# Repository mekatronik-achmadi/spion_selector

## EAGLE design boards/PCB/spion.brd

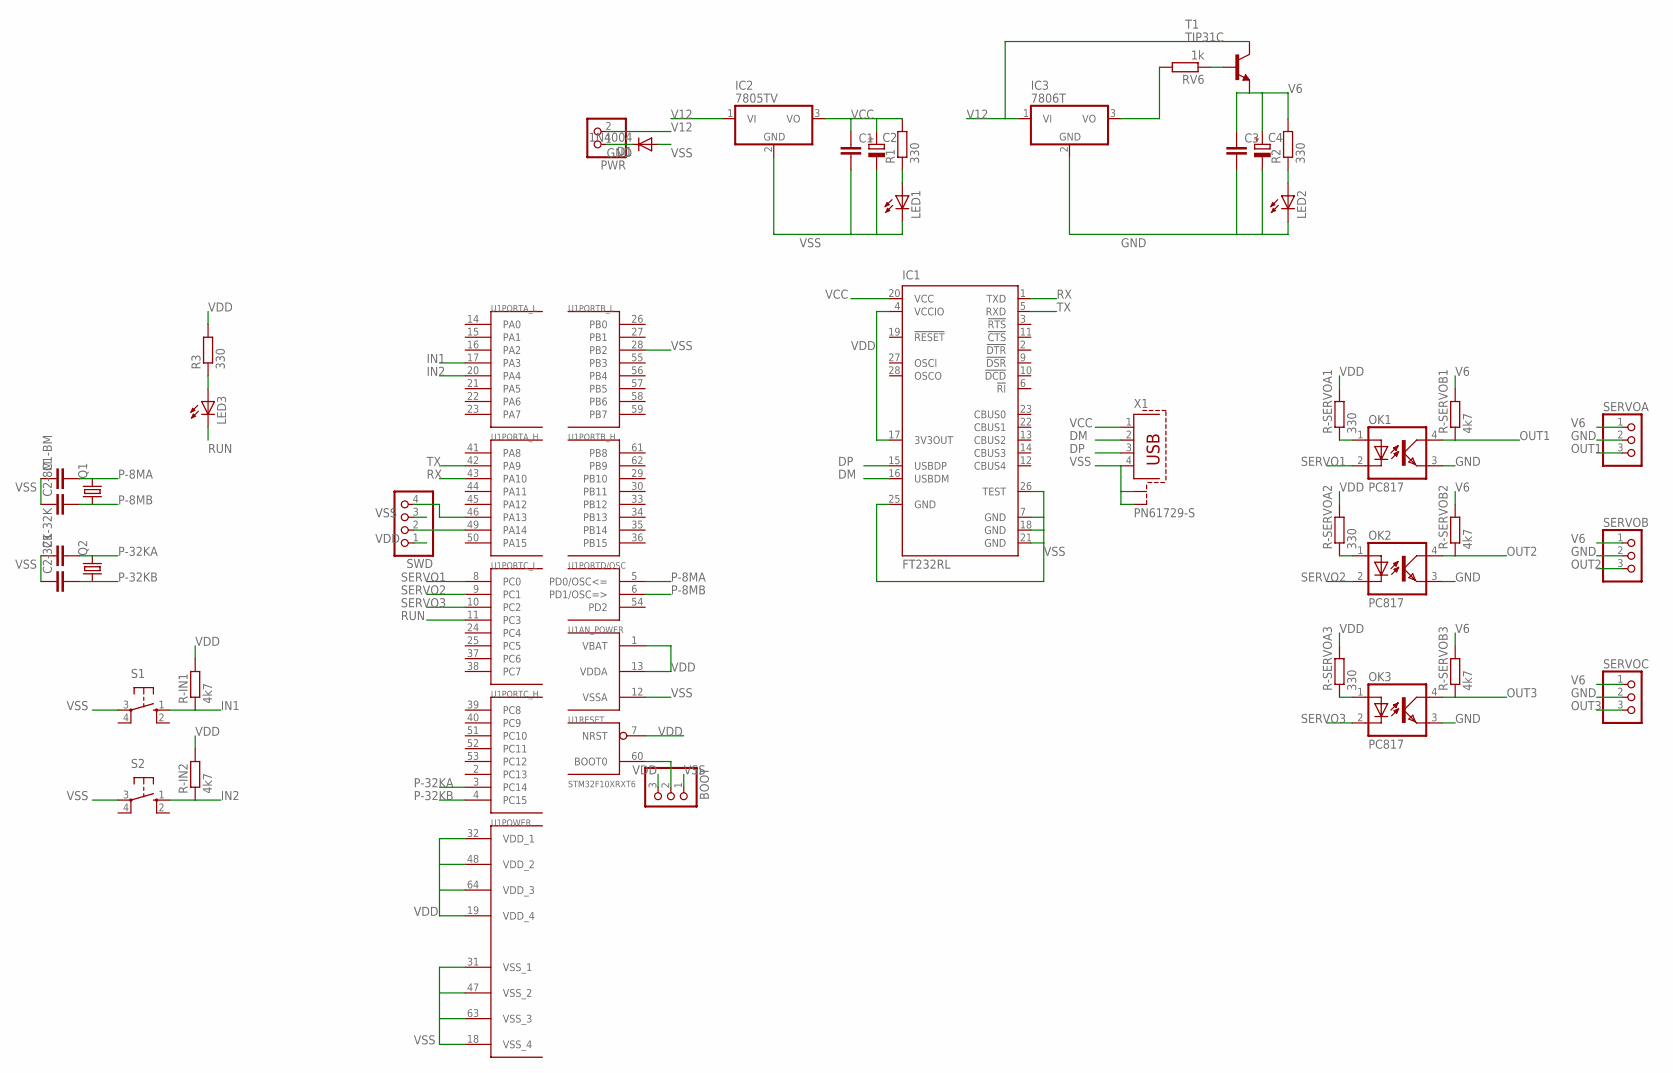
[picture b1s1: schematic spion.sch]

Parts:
BOOT: PINHD-1X3; 1X03
C1, C1-32K, C1-BM, C2-8M, C2-32K, C3: C-EU025-024X044; C025-024X044
C2, C4: CPOL-EUE2-5; E2-5
D1: 1N4004; DO41-10
IC1: FT232RL; SSOP28
IC2: 7805TV; TO220V
IC3: 7806T; TO220H
LED1, LED2, LED3: LED3MM
OK1, OK2, OK3: PC817; DIL04
PWR: PINHD-1X2; 1X02
Q1: CRYSTALHC49S; HC49/S
Q2: CRYSTALTC26V; TC26V
R1, R2, R3: 330; 0204/7
R-IN1, R-IN2: 4k7; 0204/7
R-SERVOA1, R-SERVOA2, R-SERVOA3: 330; 0204/7
R-SERVOB1, R-SERVOB2, R-SERVOB3: 4k7; 0204/7
RV6: 1k; 0204/7
S1, S2: 10-XX; B3F-10XX
SERVOA: PINHD-1X3; 1X03
SERVOB: PINHD-1X3; 1X03
SERVOC: PINHD-1X3; 1X03
SWD: PINHD-1X4; 1X04
T1: TIP31C; TO220
U1: STM32F10XRXT6; TQFP64
X1: PN61729-S

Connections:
DM: IC1.16 (USBDM), X1.2
DP: IC1.15 (USBDP), X1.3
GND: C3.2, C4.-, D1.C, IC3.2 (GND), LED2.K (C), OK1.3 (EMIT), OK2.3 (EMIT), OK3.3 (EMIT), PWR.1, SERVOA.2, SERVOB.2, SERVOC.2
IN1: R-IN1.1, S1.1 (S), U1.17 (PA3)
IN2: R-IN2.1, S2.1 (S), U1.20 (PA4)
unnamed: SWD.2, U1.49 (PA14)
unnamed: SWD.4, U1.46 (PA13)
unnamed: BOOT.2, U1.60 (BOOT0)
unnamed: OK1.1 (A), R-SERVOA1.1
unnamed: LED3.A, R3.1
unnamed: IC3.3 (VO), RV6.2
unnamed: OK2.1 (A), R-SERVOA2.1
unnamed: RV6.1, T1.1 (B)
unnamed: OK3.1 (A), R-SERVOA3.1
unnamed: LED1.A, R1.1
unnamed: LED2.A, R2.1
OUT1: OK1.4 (COL), R-SERVOB1.1, SERVOA.3
OUT2: OK2.4 (COL), R-SERVOB2.1, SERVOB.3
OUT3: OK3.4 (COL), R-SERVOB3.1, SERVOC.3
P-8MA: C1-BM.2, Q1.2, U1.5 (PD0/OSC<=)
P-8MB: C2-8M.2, Q1.1, U1.6 (PD1/OSC=>)
P-32KA: C1-32K.2, Q2.2, U1.3 (PC14)
P-32KB: C2-32K.2, Q2.1, U1.4 (PC15)
RUN: LED3.K (C), U1.11 (PC3)
RX: IC1.1 (TXD), U1.43 (PA10)
SERVO1: OK1.2 (C), U1.8 (PC0)
SERVO2: OK2.2 (C), U1.9 (PC1)
SERVO3: OK3.2 (C), U1.10 (PC2)
TX: IC1.5 (RXD), U1.42 (PA9)
V6: C3.1, C4.+, R2.2, R-SERVOB1.2, R-SERVOB2.2, R-SERVOB3.2, SERVOA.1, SERVOB.1, SERVOC.1, T1.3 (E)
V12: IC2.1 (VI), IC3.1 (VI), PWR.2, T1.2 (C)
VCC: C1.1, C2.+, IC1.20 (VCC), IC2.3 (VO), R1.2, X1.1
VDD: BOOT.3, IC1.4 (VCCIO), IC1.17 (3V3OUT), R3.2, R-IN1.2, R-IN2.2, R-SERVOA1.2, R-SERVOA2.2, R-SERVOA3.2, SWD.1, U1.1 (VBAT), U1.7 (NRST), U1.13 (VDDA), U1.19 (VDD_4), U1.32 (VDD_1), U1.48 (VDD_2), U1.64 (VDD_3)
VSS: BOOT.1, C1.2, C1-32K.1, C1-BM.1, C2.-, C2-8M.1, C2-32K.1, D1.A, IC1.7 (GND), IC1.18 (GND), IC1.21 (GND), IC1.25 (GND), IC1.26 (TEST), IC2.2 (GND), LED1.K (C), S1.3, S2.3, SWD.3, U1.12 (VSSA), U1.18 (VSS_4), U1.28 (PB2), U1.31 (VSS_1), U1.47 (VSS_2), U1.63 (VSS_3), X1.4, X1.S1, X1.S2

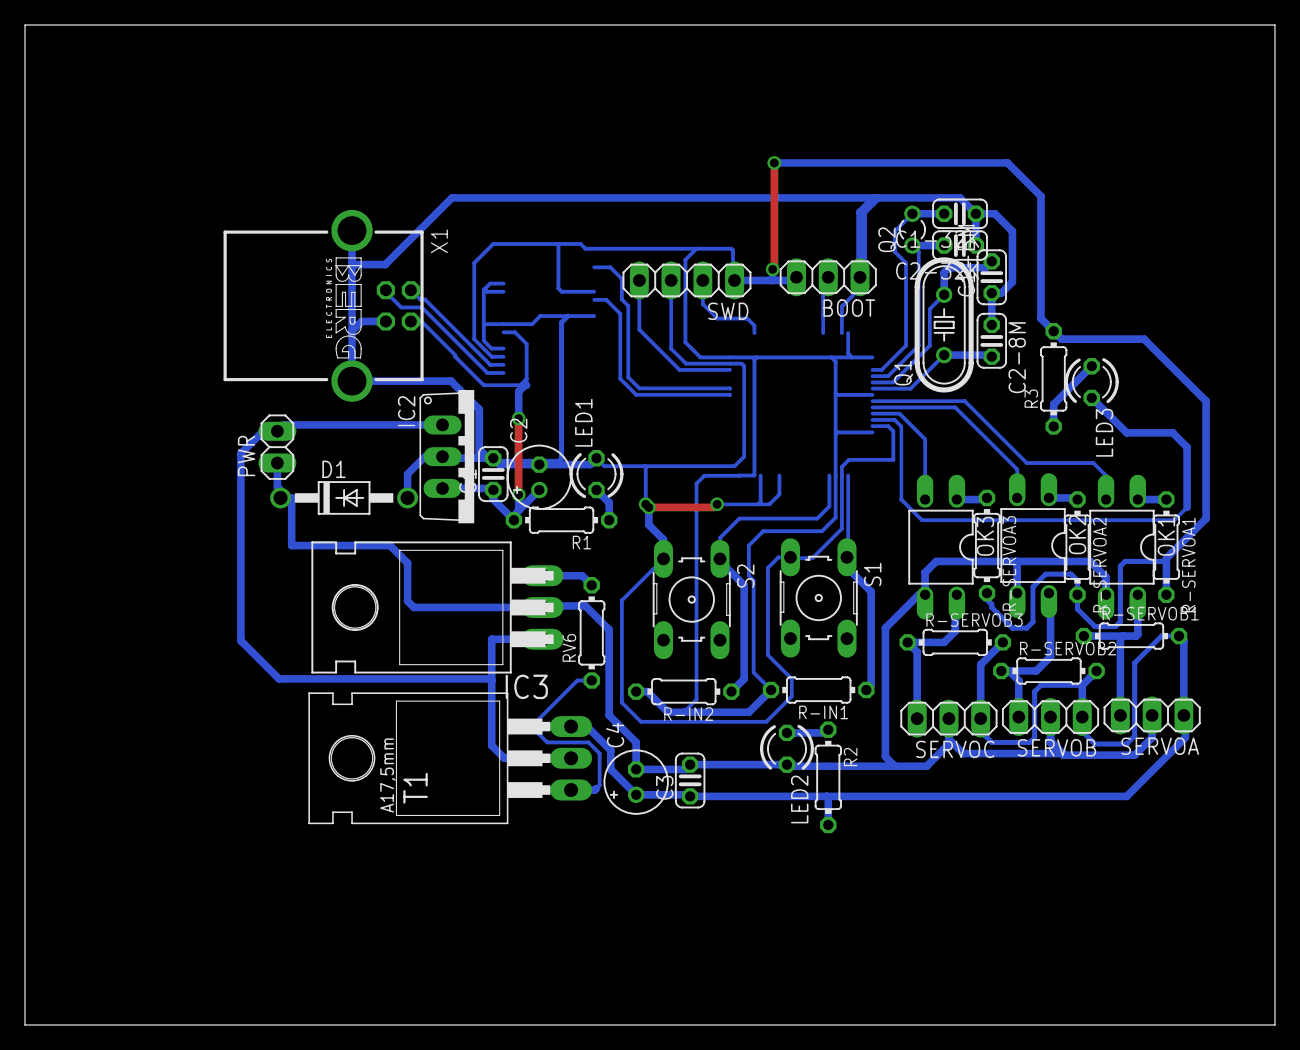
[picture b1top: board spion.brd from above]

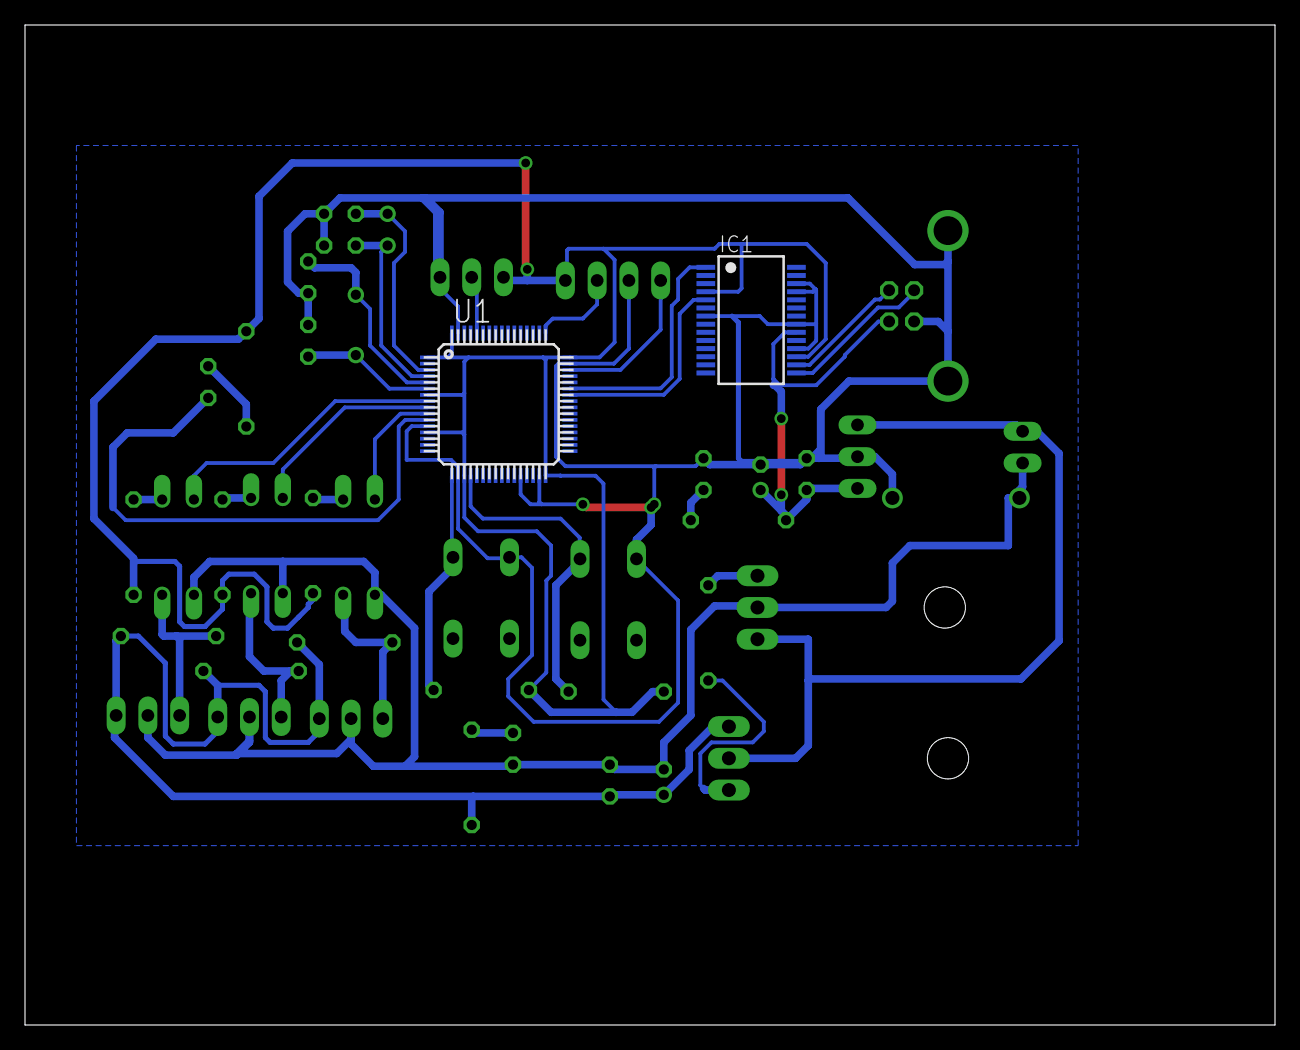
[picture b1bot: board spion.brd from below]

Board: 2 copper layers, 100.0 x 80.0 mm, 43 parts (2 on the bottom side), 34 nets.

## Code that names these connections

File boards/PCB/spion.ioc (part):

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Mcu.Name=STM32F103R(8-B)Tx
Mcu.Package=LQFP64
PA10.Mode=Asynchronous
PA10.Signal=USART1_RX
PA13.Mode=Serial-Wire
PA13.Signal=SYS_JTMS-SWDIO
PA14.Mode=Serial-Wire
PA14.Signal=SYS_JTCK-SWCLK
PA3.Signal=GPIO_Input
PA4.Signal=GPIO_Input
PA9.Mode=Asynchronous
PA9.Signal=USART1_TX
PB2.Signal=GPIO_Input
PC0.Signal=GPIO_Output
PC1.Signal=GPIO_Output
PC14-OSC32_IN.Mode=LSE-External-Oscillator
PC14-OSC32_IN.Signal=SYS_OSC32_IN
PC15-OSC32_OUT.Mode=LSE-External-Oscillator
PC15-OSC32_OUT.Signal=SYS_OSC32_OUT
PC2.Signal=GPIO_Output
PC3.Signal=GPIO_Output
PD0-OSC_IN.Mode=HSE-External-Oscillator
PD0-OSC_IN.Signal=SYS_OSC_IN
PD1-OSC_OUT.Mode=HSE-External-Oscillator
PD1-OSC_OUT.Signal=SYS_OSC_OUT

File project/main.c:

/*
    ChibiOS/RT - Copyright (C) 2006-2013 Giovanni Di Sirio

    Licensed under the Apache License, Version 2.0 (the "License");
    you may not use this file except in compliance with the License.
    You may obtain a copy of the License at

        http://www.apache.org/licenses/LICENSE-2.0

    Unless required by applicable law or agreed to in writing, software
    distributed under the License is distributed on an "AS IS" BASIS,
    WITHOUT WARRANTIES OR CONDITIONS OF ANY KIND, either express or implied.
    See the License for the specific language governing permissions and
    limitations under the License.
*/

#include "srcconf.h"

#define run 3
#define run_on palClearPad(GPIOC,run)
#define run_off palSetPad(GPIOC,run)

#define servo0 0
#define servo0_off palClearPad(GPIOC,servo0)
#define servo0_on palSetPad(GPIOC,servo0)

#define servo1 1
#define servo1_off palClearPad(GPIOC,servo1)
#define servo1_on palSetPad(GPIOC,servo1)

#define servo2 2
#define servo2_off palClearPad(GPIOC,servo2)
#define servo2_on palSetPad(GPIOC,servo2)

#define loopmax 2000
uint16_t vservo0,vservo1,vservo2;

static WORKING_AREA(wa_servo0Thread, 128);
static msg_t servo0Thread(void *arg) {
  (void)arg;
  while (TRUE) {
    
      servo0_on;
      chThdSleepMicroseconds(vservo0);

      servo0_off;
      chThdSleepMicroseconds(loopmax-vservo0);

  }
  return 0;
}

static WORKING_AREA(wa_servo1Thread, 128);
static msg_t servo1Thread(void *arg) {
  (void)arg;
  while (TRUE) {

      servo1_on;
      chThdSleepMicroseconds(vservo1);

      servo1_off;
      chThdSleepMicroseconds(loopmax-vservo1);

  }
  return 0;
}

static WORKING_AREA(wa_servo2Thread, 128);
static msg_t servo2Thread(void *arg) {
  (void)arg;
  while (TRUE) {

      servo2_on;
      chThdSleepMicroseconds(vservo2);

      servo2_off;
      chThdSleepMicroseconds(loopmax-vservo2);

  }
  return 0;
}

int main(void) {

  halInit();
  chSysInit();

  palSetPadMode(GPIOC,3,PAL_MODE_OUTPUT_PUSHPULL);
  palSetPad(GPIOC,3);
  
  vservo0=1500;
  vservo1=1500;
  vservo2=1500;
  
  palSetPadMode(GPIOC,0,PAL_MODE_OUTPUT_PUSHPULL);
  palSetPadMode(GPIOC,1,PAL_MODE_OUTPUT_PUSHPULL);
  palSetPadMode(GPIOC,2,PAL_MODE_OUTPUT_PUSHPULL);
  chThdCreateStatic(wa_servo0Thread, sizeof(wa_servo0Thread), NORMALPRIO, servo0Thread, NULL);
  chThdCreateStatic(wa_servo1Thread, sizeof(wa_servo1Thread), NORMALPRIO, servo1Thread, NULL);
  chThdCreateStatic(wa_servo2Thread, sizeof(wa_servo2Thread), NORMALPRIO, servo2Thread, NULL);

  Shell_Setup();

  while (TRUE) {
    Shell_Create();
    palTogglePad(GPIOC,3);
    chThdSleepMilliseconds(100);
  }
}

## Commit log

2014-06-24 robot arm design on DXF
2014-07-09 test run 1 success
2014-07-10 add advertise
2014-09-18 Data and Last Works
2014-10-01 opencv capturer
2014-10-08 poster
2014-10-09 poster ready to print
2014-10-09 abstrak
2014-10-23 svg format
2014-12-03 dokumentasi teknis
2014-12-07 progress dokumentasi
2014-12-08 docs
2015-02-17 document in docx
2015-02-18 progres dokumen
2015-02-18 dokumentasi
2015-02-18 dokumen
2015-02-25 serial command directly from bash using system()
2015-02-26 revision on result only
2015-02-26 revisi again
2015-03-20 reverse commands
2015-04-15 Run on Debian Unstable
2015-04-15 test moving
2015-04-15 pattern
2015-04-15 daftar paket minimal
2015-04-22 new tools
